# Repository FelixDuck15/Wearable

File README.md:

# Wearable
Montre intelligente qui est une melange d'une Whoops et d'une apple watch.
* Meilleur autonomie qu'une apple Watch
* Avoir une affiche de l'heure

## Dossier dans le projet
* pieces (the parts use for the project)
* SmartWatch (Kicad V10 project)
  * Tu dois avoir Kicad V10 pour ouvrir ce projet

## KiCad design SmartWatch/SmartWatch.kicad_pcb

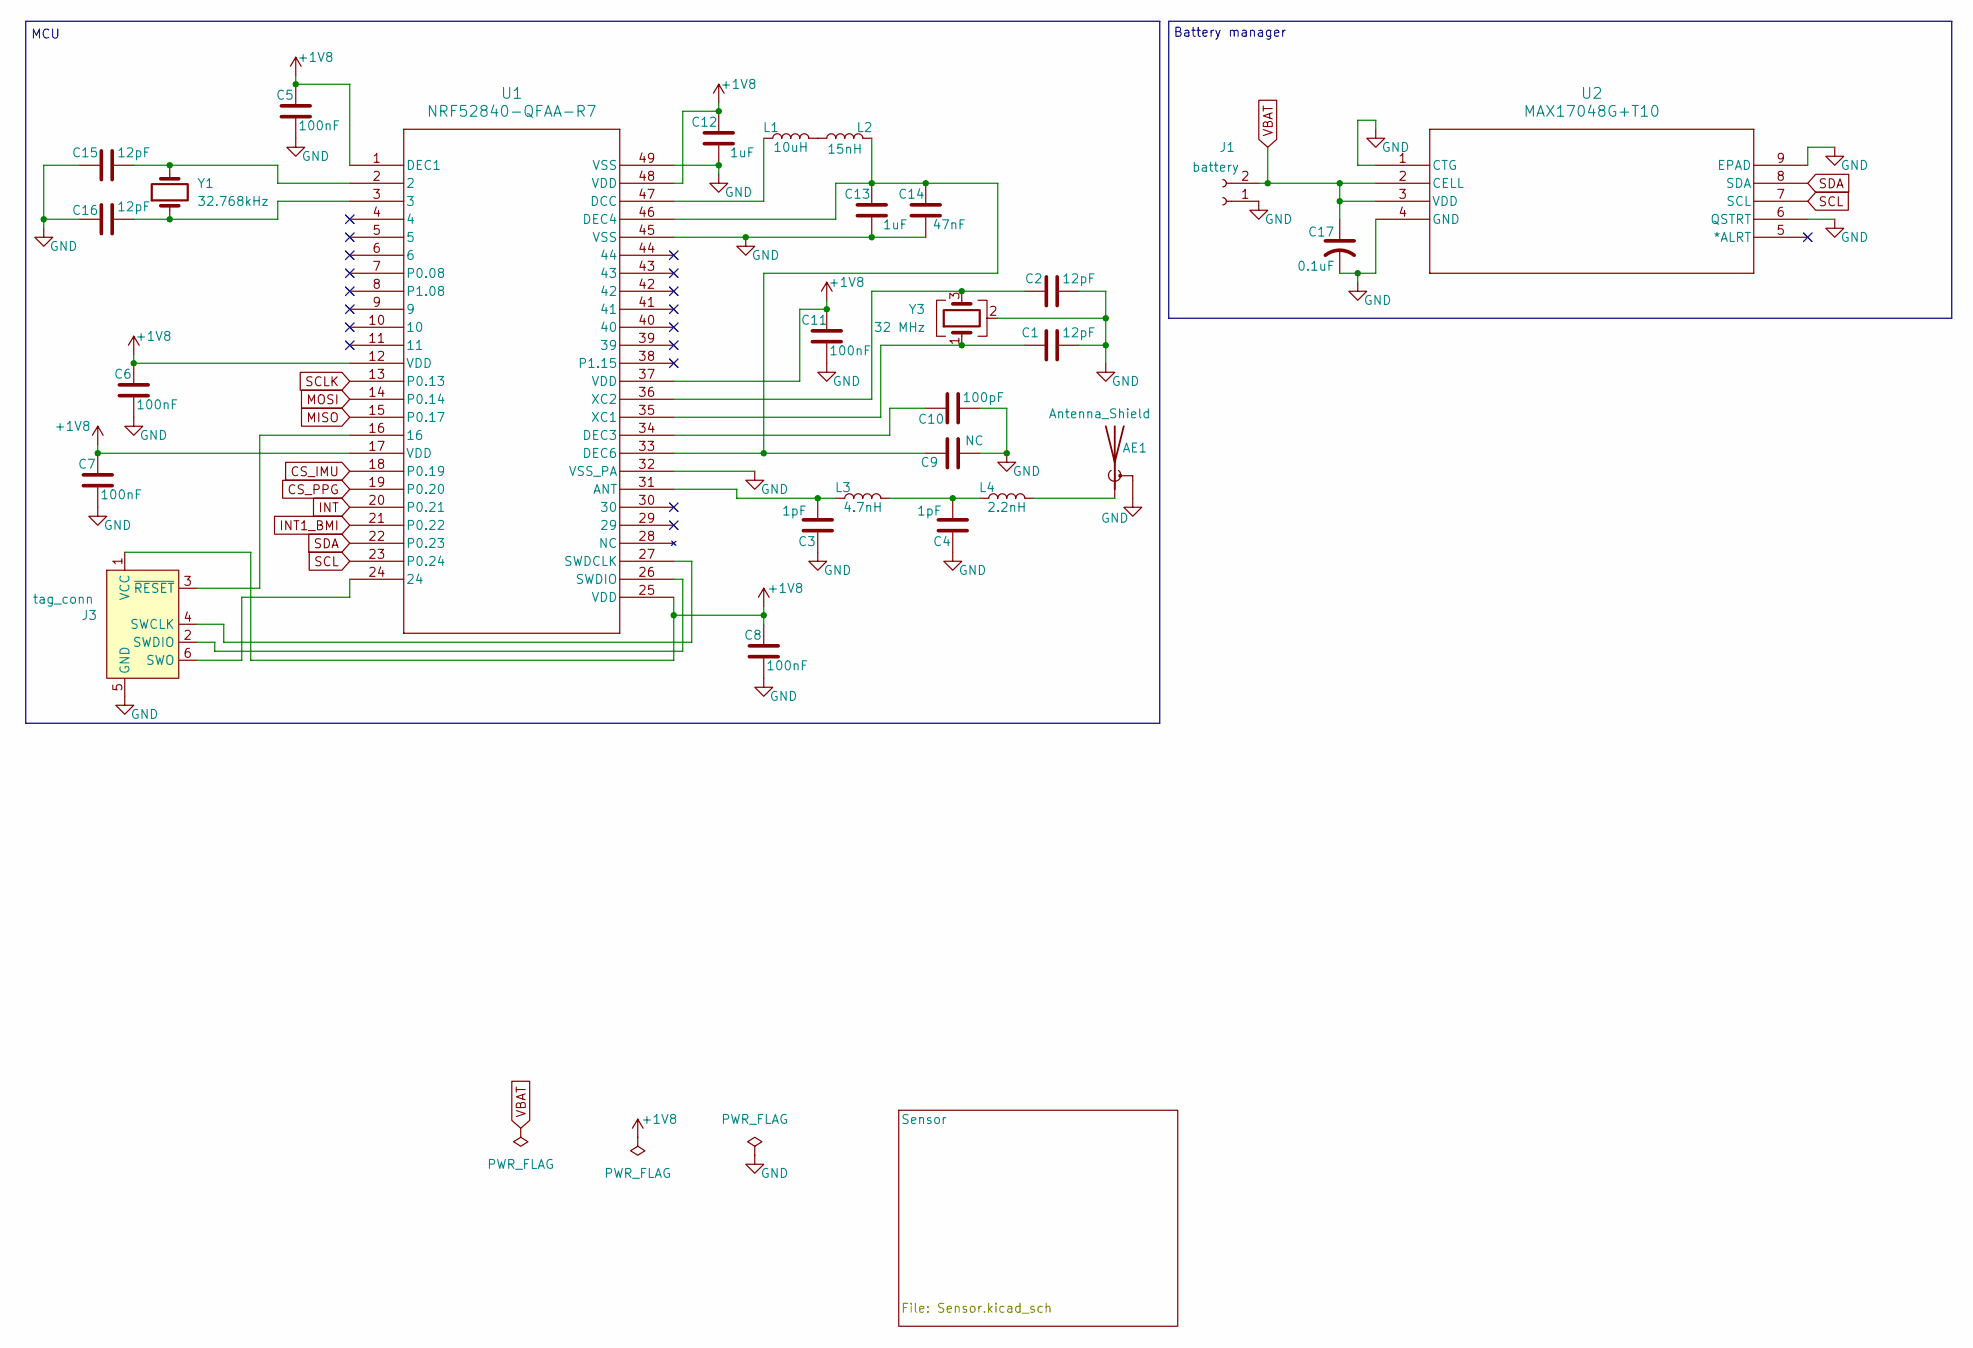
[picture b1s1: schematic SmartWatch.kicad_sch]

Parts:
AE1: Antenna_Shield; Texas_SWRA117D_2.4GHz_Right
C1, C2, C15, C16: 12pF; C_0201_0603Metric
C3, C4: 1pF; C_0201_0603Metric
C5, C6, C7, C8, C11: 100nF; C_0201_0603Metric
C9: NC; C_0201_0603Metric
C10: 100pF; C_0201_0603Metric
C12: 1uF; C_0201_0603Metric
C13: 1uF; C_0402_1005Metric
C14: 47nF; C_0201_0603Metric
C17: 0.1uF; C_0402_1005Metric
J1: battery; PinHeader_1x02_P2.54mm_Vertical
J3: tag_conn; Tag-Connect_TC2030-IDC-NL_2x03_P1.27mm_Vertical
L1: 10uH; L_0201_0603Metric
L2: 15nH; L_0201_0603Metric
L3: 4.7nH; L_0603_1608Metric
L4: 2.2nH; L_0402_1005Metric
U1: NRF52840-QFAA-R7; QFN48_NRF52840-QFAA-R7_NOR-L
U2: MAX17048G+T10; 21-0168E_T822-3_MXM-L
Y1: 32.768kHz; Crystal_SMD_2012-2Pin_2.0x1.2mm_HandSoldering
Y3: 32 MHz; Crystal_SMD_2016-4Pin_2.0x1.6mm

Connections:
+1V8: C5.2, C6.2, C7.2, C8.2, C11.2, C12.2, J3.1 (VCC), U1.1 (DEC1), U1.12 (VDD), U1.17 (VDD), U1.25 (VDD), U1.37 (VDD), U1.48 (VDD); also elsewhere on the board
CS_IMU: U1.18 (P0.19); also elsewhere on the board
CS_PPG: U1.19 (P0.20); also elsewhere on the board
GND: AE1.2 (Shield), C1.2, C2.2, C3.1, C4.1, C5.1, C6.1, C7.1, C8.1, C9.1, C10.1, C11.1, C12.1, C13.1, C14.1, C15.1, C16.1, C17.2, J1.1, J3.5 (GND), U1.32 (VSS_PA), U1.45 (VSS), U1.49 (VSS), U2.1 (CTG), U2.4 (GND), U2.6 (QSTRT), U2.9 (EPAD), Y3.2 (G), Y3.4 (G); also elsewhere on the board
INT: U1.20 (P0.21); also elsewhere on the board
INT1_BMI: U1.21 (P0.22); also elsewhere on the board
MISO: U1.15 (P0.17); also elsewhere on the board
MOSI: U1.14 (P0.14); also elsewhere on the board
unnamed: AE1.1 (A), L4.2
unnamed: C4.2, L3.2, L4.1
unnamed: C15.2, U1.2, Y1.2
unnamed: C16.2, U1.3, Y1.1
unnamed: J3.4 (SWCLK), U1.27 (SWDCLK)
unnamed: J3.2 (SWDIO), U1.26 (SWDIO)
unnamed: J3.6 (SWO), U1.24
unnamed: J3.3 (~RESET), U1.16
unnamed: L1.2, L2.1
unnamed: C3.2, L3.1, U1.31 (ANT)
unnamed: L1.1, U1.47 (DCC)
unnamed: C10.2, U1.34 (DEC3)
unnamed: C9.2, C13.2, C14.2, L2.2, U1.33 (DEC6), U1.46 (DEC4)
unnamed: C1.1, U1.35 (XC1), Y3.1
unnamed: C2.1, U1.36 (XC2), Y3.3
SCL: U1.23 (P0.24), U2.7 (SCL); also elsewhere on the board
SCLK: U1.13 (P0.13); also elsewhere on the board
SDA: U1.22 (P0.23), U2.8 (SDA); also elsewhere on the board
VBAT: C17.1, J1.2, U2.2 (CELL), U2.3 (VDD); also elsewhere on the board

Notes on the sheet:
Battery manager
MCU

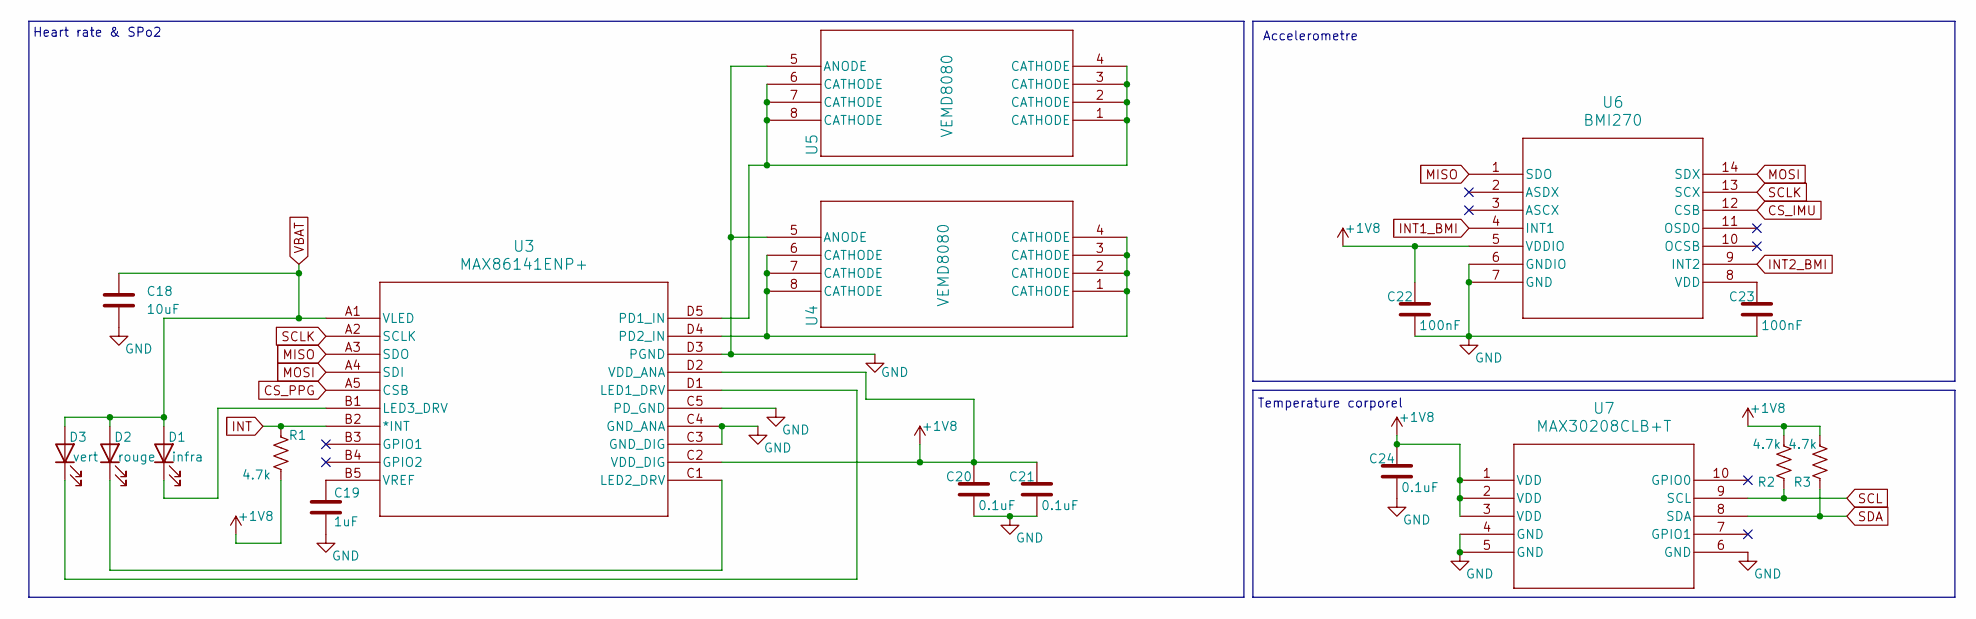
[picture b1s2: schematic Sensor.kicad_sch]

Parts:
C18: 10uF; C_0402_1005Metric
C19: 1uF; C_0402_1005Metric
C20, C21, C24: 0.1uF; C_0402_1005Metric
C22, C23: 100nF; C_0402_1005Metric
D1: infra; LED_0805_2012Metric
D2: rouge; LED_0805_2012Metric
D3: vert; LED_0805_2012Metric
R1, R2, R3: 4.7k; R_0402_1005Metric
U3: MAX86141ENP+; 21-100134A_20_MXM
U4, U5: VEMD8080; 6p550-5354p01-4_VIS
U6: BMI270; BMI270_BOS-L
U7: MAX30208CLB+T; 21-100265_MXM

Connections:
+1V8: C20.1, C21.1, C22.1, C24.1, R1.2, R2.1, R3.1, U3.C2 (VDD_DIG), U3.D2 (VDD_ANA), U6.5 (VDDIO), U7.1 (VDD), U7.2 (VDD), U7.3 (VDD); also elsewhere on the board
CS_IMU: U6.12 (CSB); also elsewhere on the board
CS_PPG: U3.A5 (CSB); also elsewhere on the board
GND: C18.2, C19.2, C20.2, C21.2, C22.2, C23.2, C24.2, U3.C3 (GND_DIG), U3.C4 (GND_ANA), U3.C5 (PD_GND), U3.D3 (PGND), U4.5 (ANODE), U5.5 (ANODE), U6.6 (GNDIO), U6.7 (GND), U7.4 (GND), U7.5 (GND), U7.6 (GND); also elsewhere on the board
INT: R1.1, U3.B2 (*INT); also elsewhere on the board
INT1_BMI: U6.4 (INT1); also elsewhere on the board
INT2_BMI: U6.9 (INT2)
MISO: U3.A3 (SDO), U6.1 (SDO); also elsewhere on the board
MOSI: U3.A4 (SDI), U6.14 (SDX); also elsewhere on the board
unnamed: D1.1 (K), U3.B1 (LED3_DRV)
unnamed: D2.1 (K), U3.C1 (LED2_DRV)
unnamed: D3.1 (K), U3.D1 (LED1_DRV)
unnamed: U3.D5 (PD1_IN), U5.1 (CATHODE), U5.2 (CATHODE), U5.3 (CATHODE), U5.4 (CATHODE), U5.6 (CATHODE), U5.7 (CATHODE), U5.8 (CATHODE)
unnamed: U3.D4 (PD2_IN), U4.1 (CATHODE), U4.2 (CATHODE), U4.3 (CATHODE), U4.4 (CATHODE), U4.6 (CATHODE), U4.7 (CATHODE), U4.8 (CATHODE)
unnamed: C19.1, U3.B5 (VREF)
unnamed: C23.1, U6.8 (VDD)
SCL: R2.2, U7.9 (SCL); also elsewhere on the board
SCLK: U3.A2 (SCLK), U6.13 (SCX); also elsewhere on the board
SDA: R3.2, U7.8 (SDA); also elsewhere on the board
VBAT: C18.1, D1.2 (A), D2.2 (A), D3.2 (A), U3.A1 (VLED); also elsewhere on the board

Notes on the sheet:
Heart rate & SPo2
Accelerometre
Temperature corporel

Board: 2 copper layers, 46 parts (0 on the bottom side), 34 nets, no tracks yet.
